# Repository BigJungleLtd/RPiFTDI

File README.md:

# RPiFTDI
A simple adapter to allow connecting of a FTDI style serial adapter to a Raspberry Pi

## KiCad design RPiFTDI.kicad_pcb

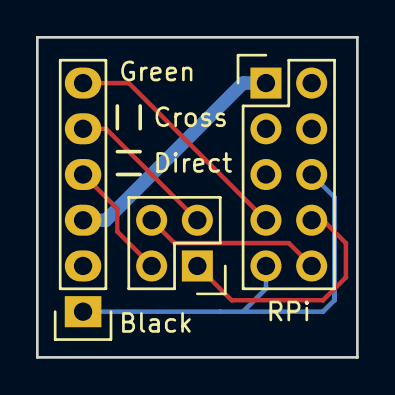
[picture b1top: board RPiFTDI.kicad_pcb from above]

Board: 2 copper layers, 17.8 x 17.8 mm, 3 parts (0 on the bottom side), 7 nets.

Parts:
JP1: RPi; Pin_Header_Straight_2x05
JP2: FTDI; Pin_Header_Straight_1x06
JP3: Config; Pin_Header_Straight_2x02

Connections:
GND: JP1.6, JP1.9, JP2.1
unnamed: JP1.1, JP2.3
unnamed: JP1.7, JP2.6
unnamed: JP1.8, JP3.1
unnamed: JP1.10, JP3.4
unnamed: JP2.4, JP3.2
unnamed: JP2.5, JP3.3

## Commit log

2015-10-16 Initial version of FTDI adapter for Raspberry Pi
